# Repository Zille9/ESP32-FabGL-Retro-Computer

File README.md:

# ESP32-Basic with FabGL VGA library + PS2-Keyboard
### Basic32+ with FabGL VGA library + PS2 PS2Controller for VGA monitor output - 2019 - 2023       
#### Ursprungsversion von: Rob Cai <rocaj74@gmail.com>
#### erweitert/modifiziert von:Reinhard Zielinski <zille09@gmail.com>                                                                   
#### Das Ergebnis ist ein kleiner Retro-Computer mit folgender Ausstattung:
- (Schaltplan siehe Ordner Schematic) 

## Hardware:
```
-ESP32 / 240MHz
-56472 Basic Bytes free
-VGA-Display 320x240 Pixel 64 Farben , AV (IO26) oder TFT-Screen 320x240 Pixel
-IO-Erweiterung mit MCP23017 (2x8 IO-Ports) + EEPROM 512kB 
-CardKb als PS2-Tastatur nutzbar (siehe Ordner <src/CardKeyBoard_neu>)
-Unterstützung von externem SPI-RAM 128kB, 512kB (Adafruit SPI-Fram) oder 2, 4 oder 8 MB PSRAM im SPI-Mode
-PS2-Keyboard 
-RTC DS3231 
-SD-Card
```

## Software:
```
Die Ursprungsversion wurde durch folgende Funktionen erweitert  

-fliesskomma Arithmetik
-Grafikfunktionen 	
-mathematische Funktionen 	
-Stringfunktionen 	
-lange Variablennamen  	
-viele zusätzliche Befehle (DATA,READ,STRG$,LEFT$,RIGHT$,MID$,POS,TAB,SPC,SIN,COS,TAN,ATN,LOG,SQR,PI usw.) 	
-erweiterte logische Operatoren (AND, OR) 	
-BIT-Manipulation &,|,%,<<,>> usw. 	
-Klammerrechnung 	
-IF THEN ELSE Abfragen 	
-Speichermonitor 	
-Exponential-Ein/Ausgabe 	
-Verschiedene Sensoren und Komponenten HC-S04, Dallas DS18S20, DHT, LCD, Neopixel-LED, BMP180 	
-Zeileneditor 
-BMP-Bilddatei-Import / Export
-Spritefunktionen (noch in der Entwicklung)
-Soundfunktionen (noch in der Entwicklung)
-integrierte Kurzhilfe
-Syntax-Hervorhebung
-Binärprogramme können mit RUN"/xxx.bin" gestartet werden - siehe Ordner <Software>

```

***Special Thanks on Guido Lehwalder and Marcelo Dantas ->RUN-CPM is a great Work!***

***Also thanks on Fabrizio Di Vittorio for the excellent FabGl-Library***

## How to compile
```
-use Arduino IDE 1.8.19
-Espressiv ESP32 Version 1.0.6
-FabGL Version 1.0.9
-copy all Files in the libraries to Arduino lib Directory
-compile and enjoy
```

```
-Startbildschirm
```

```
-Basic-Befehle
```

```
-Basic -Funktionen
```

```
-Programm Globus.Bas
```

```
-Darstellung einer BMP-Datei
```

```
-Programmlisting
```

```
Screenshot als BMP-Datei exportiert
```

```
...mit RUN kann dann auch CPM gestartet werden.
```

```
...RUN-CPM Startbildschirm , mit EXIT kehrt man wieder zum Basic32+ zurück.
```

```
...der GRID-Befehl in Aktion .
```

## Bibliotheken einbinden und Basic32+ compilieren:
```
-die im Ordner libraries liegenden Unterverzeichnisse ins Arduino libraries-Verzeichnis kopieren

-zusätzlich die FabGL-lib mit dem Bibliotheksmanager der Arduino-IDE installieren

-die Quellen befinden sich im Ordner "src/FabGL-Basic" ->kompilieren und in den ESP32 laden

-den Inhalt des Verzeichnisses SD-Card auf eine SD-Karte kopieren .... und mit ESP32+Basic loslegen :-)

Im Ordner RUN-CPM befindet sich die um den OTA-Loader erweiterte Variante, um nach Eingabe von EXIT wieder zum Basic zurückzukehren.
```

## Komponenten:

-ESP32 NodeMCU https://www.berrybase.de/esp32-nodemcu-development-board?sPartner=g_shopping&gclid=EAIaIQobChMI-fTJwNmx_wIVkupRCh1mTAgZEAQYBSABEgKjwvD_BwE

-MCP23017 https://www.reichelt.de/i-o-erweiterung-16bit-1-8-5v-seriell-i2c-dip-28-mcp-23017-e-sp-p140074.html?&trstct=pos_0&nbc=1

-FRAM 512kB https://www.adafruit.com/product/4719

-SD-Card Modul https://www.reichelt.de/arduino-sd-karten-modul-ard-module-sd-p282683.html?PROVID=2788&gclid=EAIaIQobChMIqL3-sdqx_wIVQ9rVCh1oSQiAEAQYAiABEgL9BPD_BwE

-RTC-Modul https://www.reichelt.de/entwicklerboards-praezisions-echtzeituhr-ds3231-debo-rtc-uhr2-p235506.html?PROVID=2788&gclid=EAIaIQobChMImaDrzNqx_wIVQs7VCh1VowhwEAQYBCABEgLQoPD_BwE

-siehe auch BOOM-List im Ordner Schematic ->folgt bald

 ### Author:Reinhard Zielinski <zille09@gmail.com> April 2021

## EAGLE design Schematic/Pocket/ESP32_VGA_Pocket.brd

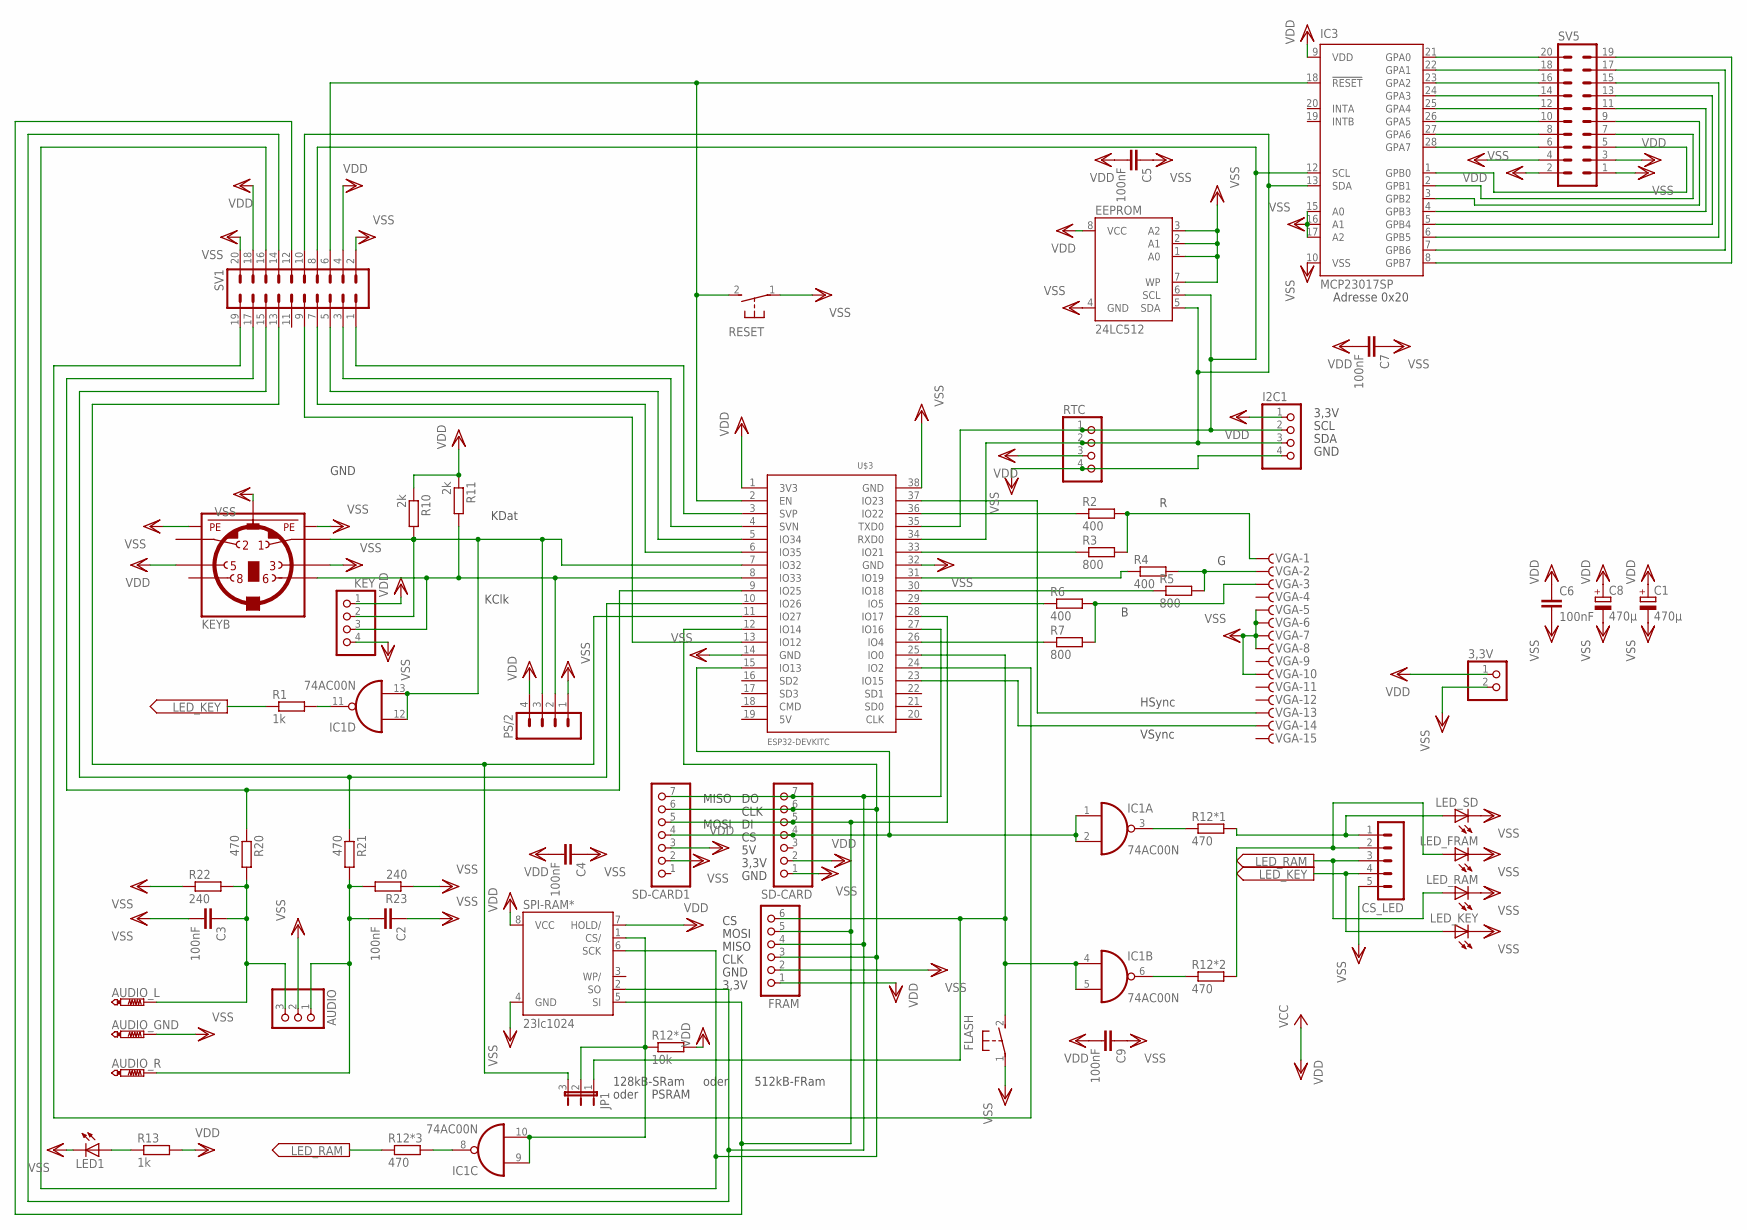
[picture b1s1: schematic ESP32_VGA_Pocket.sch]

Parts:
3,3V: PINHD-1X2; 1X02
AUDIO: PINHD-1X3; 1X03
AUDIO_GND: PTR1PAD1-13Y; P1-13Y
AUDIO_L: PTR1PAD1-13Y; P1-13Y
AUDIO_R: PTR1PAD1-13Y; P1-13Y
C1, C8: 470µ; E3,5-10
C2, C3, C4, C5, C6, C7, C9: 100nF; C025-030X050
CS_LED: MA05-1
EEPROM: 24LC512; DIL08
FLASH: 31-XX; B3F-31XX; MPN B3F-3100
FRAM: PINHD-1X6; 1X06
I2C1: PINHD-1X4; 1X04
IC1: 74AC00N; DIL14
IC3: MCP23017SP; DIL28-3; MPN MCP23017-E/SO
JP1: JP2E; JP2
KEY: PINHD-1X4; 1X04
KEYB: MINI_DIN_6; M_DIN6
LED1: LED5MM
LED_FRAM: LED5MM
LED_KEY: LED5MM
LED_RAM: LED5MM
LED_SD: LED5MM
PS/2: MA04-1
R1, R13: 1k; 0204/7
R2, R4, R6: 400; 0204/7
R3, R5, R7: 800; 0204/7
R10, R11: 2k; 0204/7
R12*: 10k; 0204/7
R12*1, R12*2, R12*3, R20, R21: 470; 0204/7
R22, R23: 240; 0204/7
RESET: 31-XX; B3F-31XX
RTC: PINHD-1X4; 1X04
SD-CARD, SD-CARD1: PINHD-1X7; 1X07
SPI-RAM*: 23lc1024; DIL08
SV1, SV5: MA10-2
U$3: ESP32DEVKITC; ESP32-DEVKITC
VGA: F15HDHS; HDF15H

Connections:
AUDIO1: AUDIO.3, AUDIO_L.TP, C3.1, R20.2, R22.2
AUDIO2: AUDIO.1, AUDIO_R.TP, C2.2, R21.2, R23.2
CLK: FRAM.3, SD-CARD.6, SD-CARD1.6, SPI-RAM*.6 (SCK), SV1.16, U$3.12 (IO14)
CLK_K: KEY.3, KEYB.6, PS/2.2, R11.2, U$3.8 (IO33)
CS_RAM: IC1.9 (I0), IC1.10 (I1), JP1.2, R12*.1, SPI-RAM*.1 (CS/)
CS_SD: IC1.1 (I0), IC1.2 (I1), SD-CARD.4, SD-CARD1.4, U$3.15 (IO13)
DAT_K: IC1.12 (I0), IC1.13 (I1), KEY.2, KEYB.1, PS/2.3, R10.2, U$3.7 (IO32)
FLASH: FLASH.2 (S), FRAM.6, IC1.4 (I0), IC1.5 (I1), JP1.1, U$3.25 (IO0)
GND: IC1.7 (GND)
IO2: SV1.19, U$3.24 (IO2)
IO12: SV1.9, U$3.13 (IO12)
IO27: JP1.3, SV1.13, U$3.11 (IO27)
IO34: SV1.5, U$3.5 (IO34)
IO35: SV1.7, U$3.6 (IO35)
IO36: SV1.1, U$3.3 (SVP)
IO39: SV1.3, U$3.4 (SVN)
LED_FRAM: CS_LED.2, LED_FRAM.A, R12*2.2
LED_KEY: CS_LED.4, LED_KEY.A, R1.1
LED_RAM: CS_LED.3, LED_RAM.A, R12*3.1
LED_SD: CS_LED.1, LED_SD.A, R12*1.2
MISO: FRAM.4, SD-CARD.7, SD-CARD1.7, SPI-RAM*.2 (SO), SV1.14, U$3.27 (IO16)
MOSI: FRAM.5, SD-CARD.5, SD-CARD1.5, SPI-RAM*.5 (SI), SV1.12, U$3.28 (IO17)
unnamed: R20.1, SV1.17, U$3.9 (IO25)
unnamed: IC1.3 (O), R12*1.1
unnamed: R21.1, SV1.15, U$3.10 (IO26)
unnamed: IC1.11 (O), R1.2
unnamed: IC1.6 (O), R12*2.1
unnamed: IC1.8 (O), R12*3.2
unnamed: LED1.A, R13.1
unnamed: IC3.1 (GPB0), SV5.5
unnamed: IC3.21 (GPA0), SV5.20
unnamed: IC3.22 (GPA1), SV5.18
unnamed: IC3.23 (GPA2), SV5.16
unnamed: IC3.24 (GPA3), SV5.14
unnamed: IC3.25 (GPA4), SV5.12
unnamed: IC3.26 (GPA5), SV5.10
unnamed: IC3.27 (GPA6), SV5.8
unnamed: IC3.28 (GPA7), SV5.6
unnamed: IC3.2 (GPB1), SV5.7
unnamed: IC3.3 (GPB2), SV5.9
unnamed: IC3.4 (GPB3), SV5.11
unnamed: IC3.5 (GPB4), SV5.13
unnamed: IC3.6 (GPB5), SV5.15
unnamed: IC3.7 (GPB6), SV5.17
unnamed: IC3.8 (GPB7), SV5.19
unnamed: R6.2, R7.2, VGA.3
unnamed: R4.2, R5.2, VGA.2
unnamed: R2.2, R3.2, VGA.1
unnamed: R2.1, U$3.36 (IO22)
unnamed: R3.1, U$3.33 (IO21)
unnamed: R4.1, U$3.31 (IO19)
unnamed: R5.1, U$3.30 (IO18)
unnamed: R6.1, U$3.29 (IO5)
unnamed: R7.1, U$3.26 (IO4)
unnamed: U$3.37 (IO23), VGA.13
unnamed: U$3.23 (IO15), VGA.14
RESET: IC3.18 (!RESET), RESET.2 (S), SV1.6, U$3.2 (EN)
SCL: EEPROM.6 (SCL), I2C1.2, IC3.12 (SCL), RTC.1, SV1.8, U$3.35 (TXD0)
SDA: EEPROM.5 (SDA), I2C1.3, IC3.13 (SDA), RTC.2, SV1.10, U$3.34 (RXD0)
VDD: 3,3V.1, C1.+, C4.2, C5.2, C6.1, C7.2, C8.+, C9.2, EEPROM.8 (VCC), FRAM.1, I2C1.1, IC1.14 (VCC), IC3.9 (VDD), KEY.1, KEYB.5, PS/2.4, R10.1, R11.1, R12*.2, R13.2, RTC.3, SD-CARD.2, SD-CARD1.3, SPI-RAM*.7 (HOLD/), SPI-RAM*.8 (VCC), SV1.4, SV1.18, SV5.3, SV5.4, U$3.1 (3V3)
VSS: 3,3V.2, AUDIO.2, AUDIO_GND.TP, C1.-, C2.1, C3.2, C4.1, C5.1, C6.2, C7.1, C8.-, C9.1, CS_LED.5, EEPROM.1 (A0), EEPROM.2 (A1), EEPROM.3 (A2), EEPROM.4 (GND), EEPROM.7 (WP), FLASH.1, FRAM.2, I2C1.4, IC3.10 (VSS), IC3.15 (A0), IC3.16 (A1), IC3.17 (A2), KEY.4, KEYB.3, KEYB.SH1 (PE1), KEYB.SH2 (PE2), KEYB.SH3 (PE3), LED1.K (C), LED_FRAM.K (C), LED_KEY.K (C), LED_RAM.K (C), LED_SD.K (C), PS/2.1, R22.1, R23.1, RESET.1, RTC.4, SD-CARD.1, SD-CARD1.2, SPI-RAM*.4 (GND), SV1.2, SV1.20, SV5.1, SV5.2, U$3.14 (GND), U$3.32 (GND), U$3.38 (GND), VGA.5, VGA.6, VGA.7, VGA.8, VGA.10

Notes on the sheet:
CLK
MISO
MOSI
KDat
KClk
VSync
HSync
GND
SCL
SDA
3,3V
128kB-SRam
512kB-FRam
oder
Adresse 0x20
PSRAM

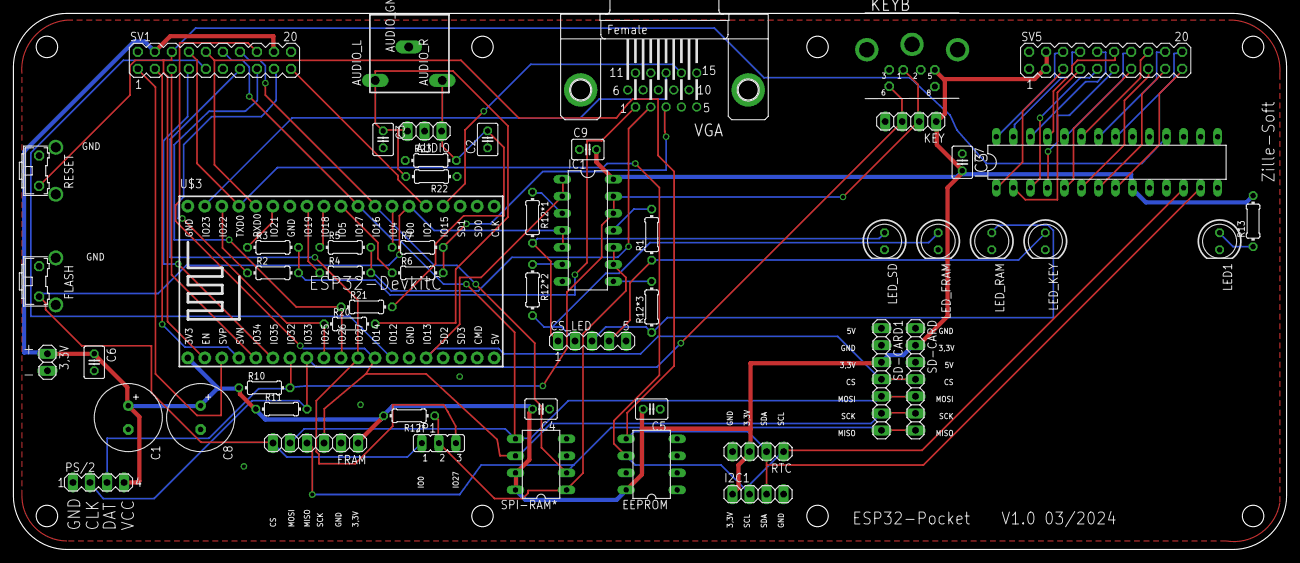
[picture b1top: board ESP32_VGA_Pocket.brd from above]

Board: 2 copper layers, 190.0 x 80.0 mm, 57 parts (0 on the bottom side), 60 nets.

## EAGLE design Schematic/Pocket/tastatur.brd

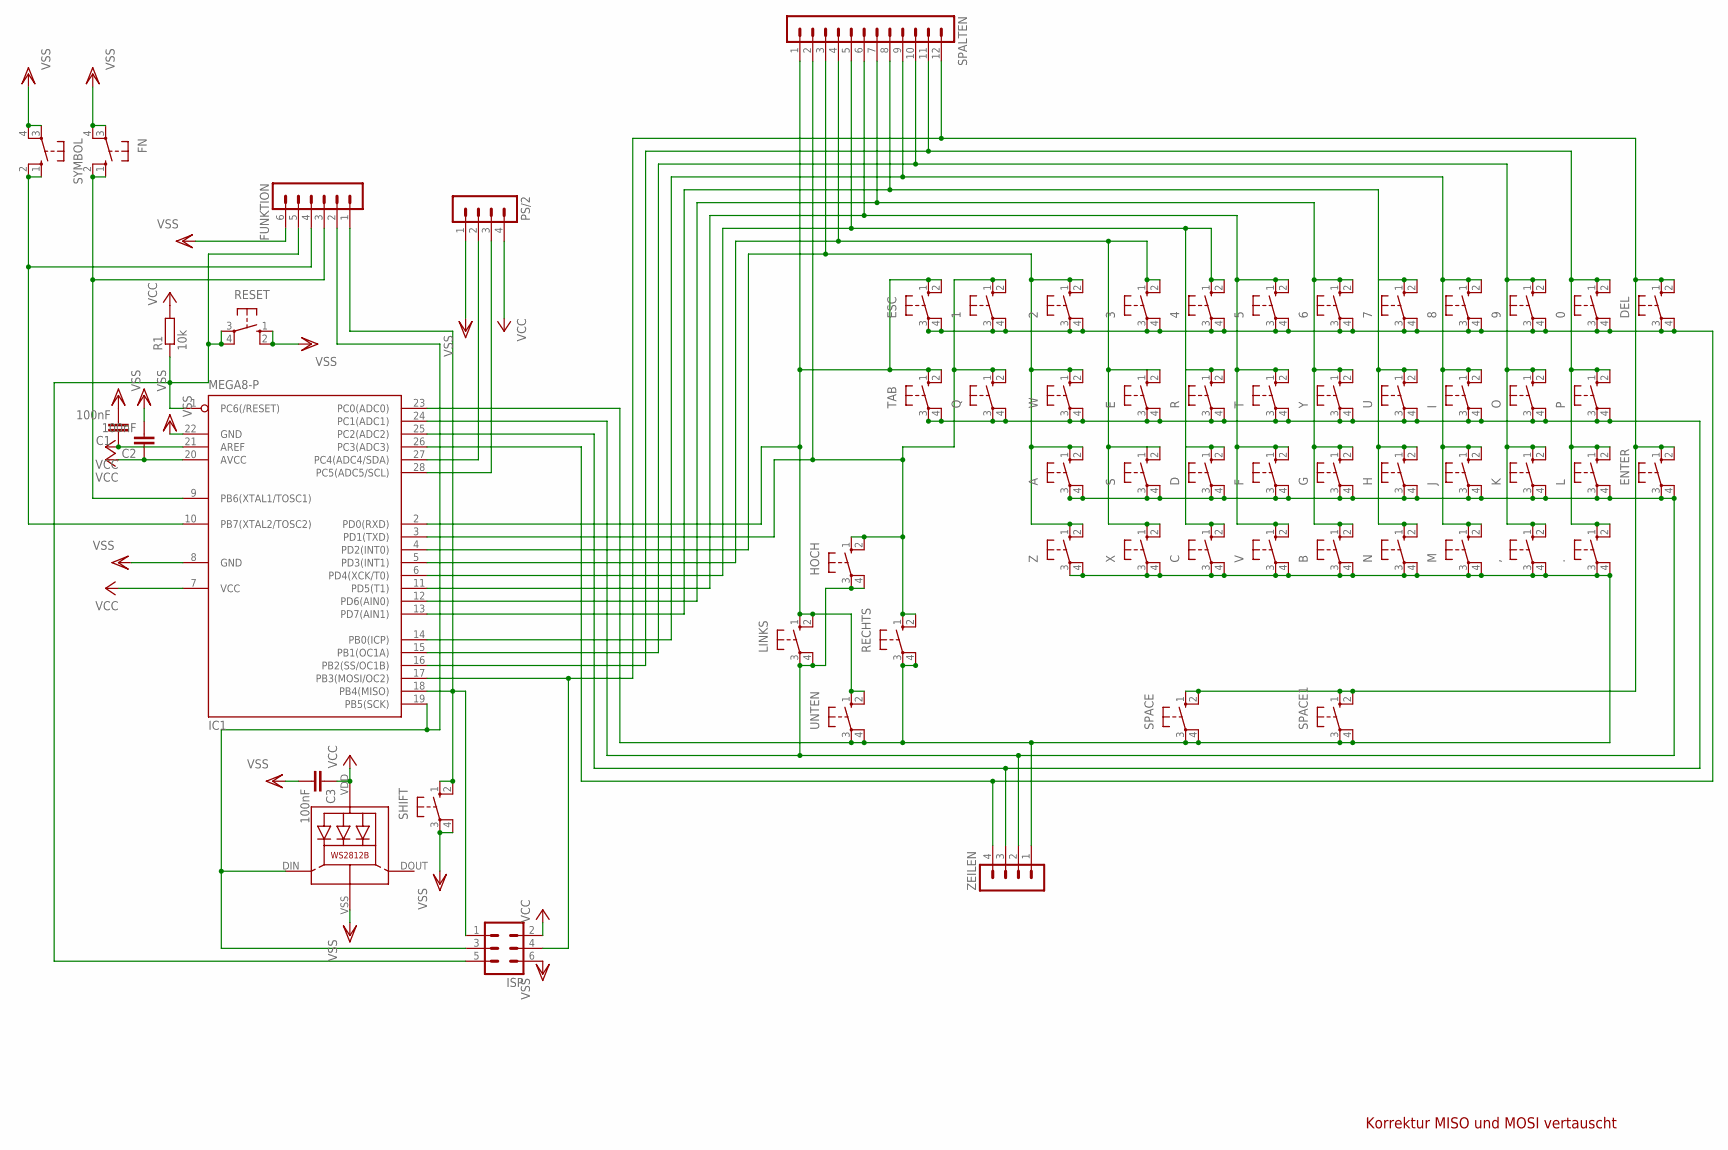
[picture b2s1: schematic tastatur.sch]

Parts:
0, 1, 2, 3, 4, 5, 6, 7, 8, 9, .: 40-XX; B3F-40XX
,: 40-XX; B3F-40XX
A: 40-XX; B3F-40XX
B: 40-XX; B3F-40XX
C: 40-XX; B3F-40XX
C1, C2, C3: 100nF; C025-025X050
D: 40-XX; B3F-40XX
DEL: 40-XX; B3F-40XX
E: 40-XX; B3F-40XX
ENTER: 40-XX; B3F-40XX
ESC: 40-XX; B3F-40XX
F: 40-XX; B3F-40XX
FN: 40-XX; B3F-40XX
FUNKTION: MA06-1
G: 40-XX; B3F-40XX
H: 40-XX; B3F-40XX
HOCH: 40-XX; B3F-40XX; MPN B3F-4000
I: 40-XX; B3F-40XX
IC1: MEGA8-P; DIL28-3
ISP: ML6L
J: 40-XX; B3F-40XX
K: 40-XX; B3F-40XX
L: 40-XX; B3F-40XX
LED1: WS2812B
LINKS: 40-XX; B3F-40XX; MPN B3F-4000
M: 40-XX; B3F-40XX
N: 40-XX; B3F-40XX
O: 40-XX; B3F-40XX
P: 40-XX; B3F-40XX
PS/2: MA04-1
Q: 40-XX; B3F-40XX
R: 40-XX; B3F-40XX
R1: 10k; 0204/7
RECHTS: 40-XX; B3F-40XX; MPN B3F-4000
RESET: 10-XX; B3F-10XX
S: 40-XX; B3F-40XX
SHIFT: 40-XX; B3F-40XX
SPACE: 40-XX; B3F-40XX; MPN B3F-4000
SPACE1: 40-XX; B3F-40XX
SPALTEN: MA12-1
SYMBOL: 40-XX; B3F-40XX
T: 40-XX; B3F-40XX
TAB: 40-XX; B3F-40XX
U: 40-XX; B3F-40XX
UNTEN: 40-XX; B3F-40XX; MPN B3F-4000
V: 40-XX; B3F-40XX
W: 40-XX; B3F-40XX
X: 40-XX; B3F-40XX
Y: 40-XX; B3F-40XX
Z: 40-XX; B3F-40XX
ZEILEN: MA04-1

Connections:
A0: ,.3, ,.4 (P1), ..3, ..4 (P1), B.3, B.4 (P1), C.3, C.4 (P1), IC1.23 (PC0(ADC0)), M.3, M.4 (P1), N.3, N.4 (P1), RECHTS.3, RECHTS.4 (P1), SPACE.3, SPACE.4 (P1), SPACE1.3, SPACE1.4 (P1), UNTEN.3, UNTEN.4 (P1), V.3, V.4 (P1), X.3, X.4 (P1), Z.3, Z.4 (P1), ZEILEN.1
A1: A.3, A.4 (P1), D.3, D.4 (P1), ENTER.3, ENTER.4 (P1), F.3, F.4 (P1), G.3, G.4 (P1), H.3, H.4 (P1), HOCH.3, HOCH.4 (P1), IC1.24 (PC1(ADC1)), J.3, J.4 (P1), K.3, K.4 (P1), L.3, L.4 (P1), LINKS.3, LINKS.4 (P1), S.3, S.4 (P1), ZEILEN.2
A2: E.3, E.4 (P1), I.3, I.4 (P1), IC1.25 (PC2(ADC2)), O.3, O.4 (P1), P.3, P.4 (P1), Q.3, Q.4 (P1), R.3, R.4 (P1), T.3, T.4 (P1), TAB.3, TAB.4 (P1), U.3, U.4 (P1), W.3, W.4 (P1), Y.3, Y.4 (P1), ZEILEN.3
A3: 0.3, 0.4 (P1), 1.3, 1.4 (P1), 2.3, 2.4 (P1), 3.3, 3.4 (P1), 4.3, 4.4 (P1), 5.3, 5.4 (P1), 6.3, 6.4 (P1), 7.3, 7.4 (P1), 8.3, 8.4 (P1), 9.3, 9.4 (P1), DEL.3, DEL.4 (P1), ESC.3, ESC.4 (P1), IC1.26 (PC3(ADC3)), ZEILEN.4
CLK: IC1.27 (PC4(ADC4/SDA)), PS/2.2
D0: ESC.1 (S), ESC.2 (S1), IC1.2 (PD0(RXD)), LINKS.1 (S), LINKS.2 (S1), SPALTEN.1, TAB.1 (S), TAB.2 (S1), UNTEN.1 (S), UNTEN.2 (S1)
D1: 1.1 (S), 1.2 (S1), HOCH.1 (S), HOCH.2 (S1), IC1.3 (PD1(TXD)), Q.1 (S), Q.2 (S1), RECHTS.1 (S), RECHTS.2 (S1), SPALTEN.2
D2: 2.1 (S), 2.2 (S1), A.1 (S), A.2 (S1), IC1.4 (PD2(INT0)), SPALTEN.3, W.1 (S), W.2 (S1), Z.1 (S), Z.2 (S1)
D3: 3.1 (S), 3.2 (S1), E.1 (S), E.2 (S1), IC1.5 (PD3(INT1)), S.1 (S), S.2 (S1), SPALTEN.4, X.1 (S), X.2 (S1)
D4: 4.1 (S), 4.2 (S1), C.1 (S), C.2 (S1), D.1 (S), D.2 (S1), IC1.6 (PD4(XCK/T0)), R.1 (S), R.2 (S1), SPALTEN.5
D5: 5.1 (S), 5.2 (S1), F.1 (S), F.2 (S1), IC1.11 (PD5(T1)), SPALTEN.6, T.1 (S), T.2 (S1), V.1 (S), V.2 (S1)
D6: 6.1 (S), 6.2 (S1), B.1 (S), B.2 (S1), G.1 (S), G.2 (S1), IC1.12 (PD6(AIN0)), SPALTEN.7, Y.1 (S), Y.2 (S1)
D7: 7.1 (S), 7.2 (S1), H.1 (S), H.2 (S1), IC1.13 (PD7(AIN1)), N.1 (S), N.2 (S1), SPALTEN.8, U.1 (S), U.2 (S1)
D8: 8.1 (S), 8.2 (S1), I.1 (S), I.2 (S1), IC1.14 (PB0(ICP)), J.1 (S), J.2 (S1), M.1 (S), M.2 (S1), SPALTEN.9
D9: 9.1 (S), 9.2 (S1), ,.1 (S), ,.2 (S1), IC1.15 (PB1(OC1A)), K.1 (S), K.2 (S1), O.1 (S), O.2 (S1), SPALTEN.10
D10: 0.1 (S), 0.2 (S1), ..1 (S), ..2 (S1), IC1.16 (PB2(SS/OC1B)), L.1 (S), L.2 (S1), P.1 (S), P.2 (S1), SPALTEN.11
D11: DEL.1 (S), DEL.2 (S1), ENTER.1 (S), ENTER.2 (S1), IC1.17 (PB3(MOSI/OC2)), ISP.4, SPACE.1 (S), SPACE.2 (S1), SPACE1.1 (S), SPACE1.2 (S1), SPALTEN.12
DAT: IC1.28 (PC5(ADC5/SCL)), PS/2.3
DIN: FUNKTION.2, IC1.19 (PB5(SCK)), ISP.3, LED1.DIN (DI)
FN: FN.1 (S), FN.2 (S1), FUNKTION.3, IC1.9 (PB6(XTAL1/TOSC1))
RESET: FUNKTION.5, IC1.1 (PC6(/RESET)), ISP.5, R1.1, RESET.3, RESET.4 (P1)
SHIFT: FUNKTION.1, IC1.18 (PB4(MISO)), ISP.1, SHIFT.1 (S), SHIFT.2 (S1)
SYMBOL: FUNKTION.4, IC1.10 (PB7(XTAL2/TOSC2)), SYMBOL.1 (S), SYMBOL.2 (S1)
VCC: C1.1, C2.1, C3.1, IC1.7 (VCC), IC1.20 (AVCC), IC1.21 (AREF), ISP.2, LED1.VDD, PS/2.4, R1.2
VSS: C1.2, C2.2, C3.2, FN.3, FN.4 (P1), FUNKTION.6, IC1.8 (GND), IC1.22 (GND), ISP.6, LED1.VSS (GND), PS/2.1, RESET.1 (S), RESET.2 (S1), SHIFT.3, SHIFT.4 (P1), SYMBOL.3, SYMBOL.4 (P1)

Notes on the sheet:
Korrektur MISO und MOSI vertauscht

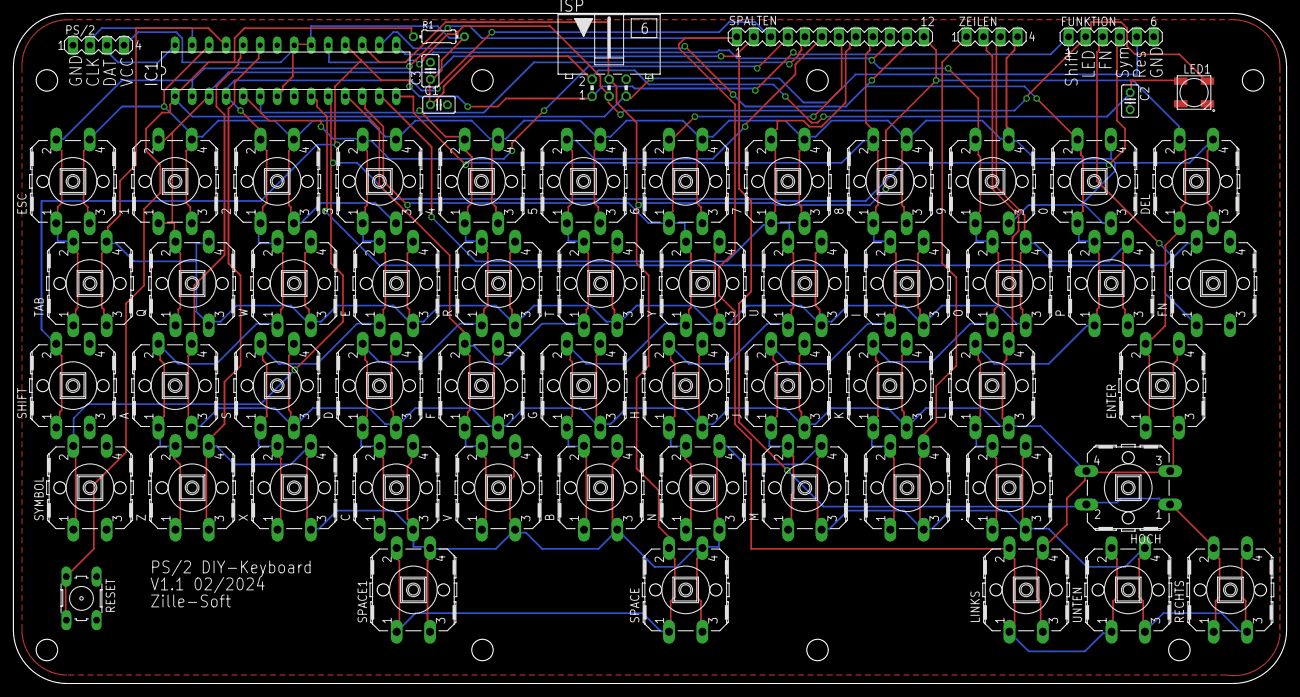
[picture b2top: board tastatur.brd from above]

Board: 2 copper layers, 190.0 x 100.0 mm, 63 parts (0 on the bottom side), 25 nets.

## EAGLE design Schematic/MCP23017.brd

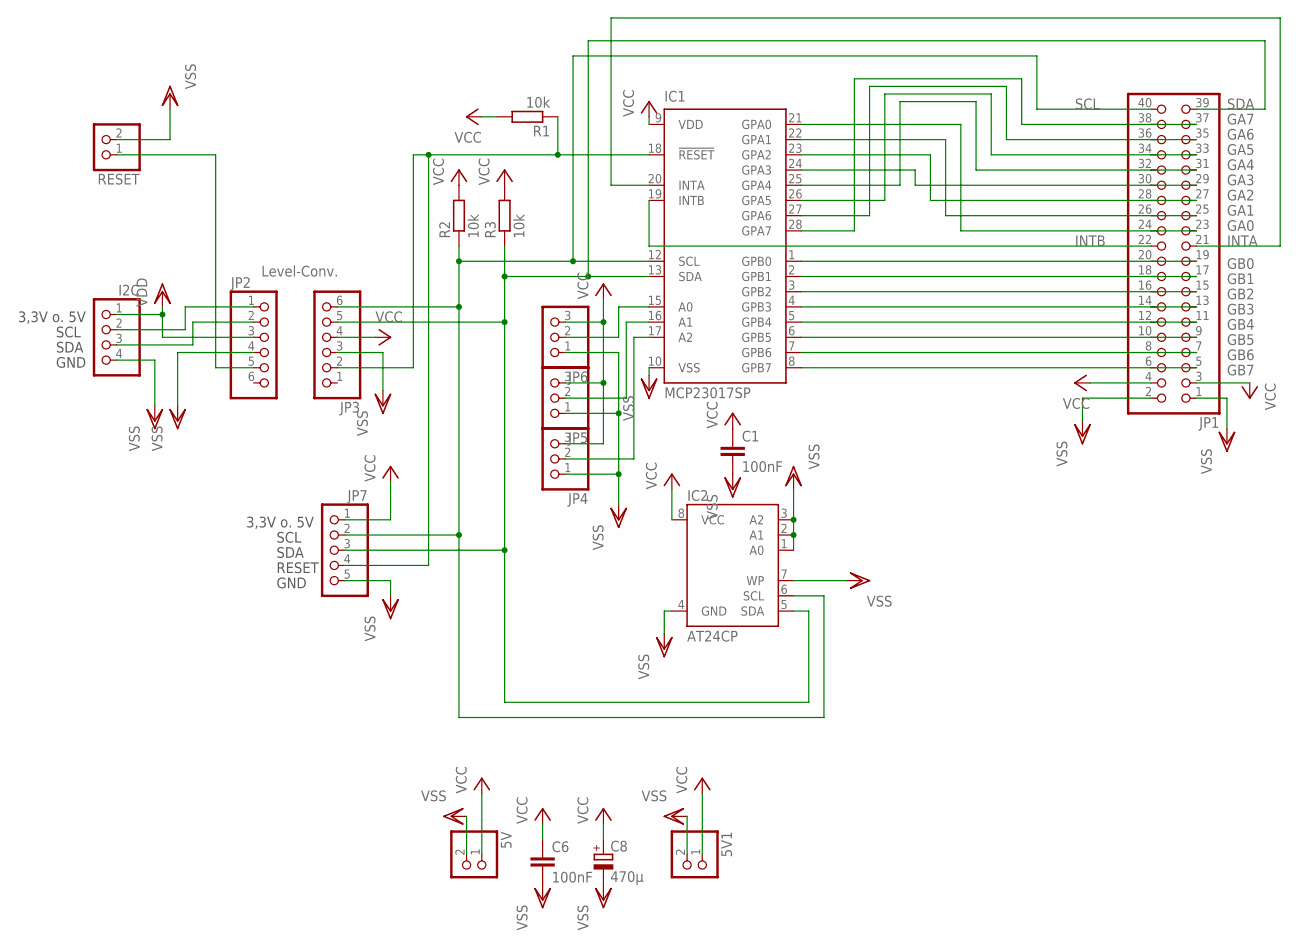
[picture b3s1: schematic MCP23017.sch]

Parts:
5V, 5V1: PINHD-1X2; 1X02
C1, C6: 100nF; C025-030X050
C8: 470µ; E3,5-10
I2C: PINHD-1X4; 1X04
IC1: MCP23017SP; DIL28-3
IC2: AT24CP; DIL08
JP1: PINHD-2X20; 2X20
JP2, JP3: PINHD-1X6; 1X06
JP4, JP5, JP6: PINHD-1X3; 1X03
JP7: PINHD-1X5; 1X05
R1, R2, R3: 10k; 0207/10
RESET: PINHD-1X2; 1X02

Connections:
A0: IC1.21 (GPA0), JP1.23, JP1.24
A1: IC1.22 (GPA1), JP1.25, JP1.26
A2: IC1.23 (GPA2), JP1.27, JP1.28
A3: IC1.24 (GPA3), JP1.29, JP1.30
A4: IC1.25 (GPA4), JP1.31, JP1.32
A5: IC1.26 (GPA5), JP1.33, JP1.34
A6: IC1.27 (GPA6), JP1.35, JP1.36
A7: IC1.28 (GPA7), JP1.37, JP1.38
B0: IC1.1 (GPB0), JP1.19, JP1.20
B1: IC1.2 (GPB1), JP1.17, JP1.18
B2: IC1.3 (GPB2), JP1.15, JP1.16
B3: IC1.4 (GPB3), JP1.13, JP1.14
B4: IC1.5 (GPB4), JP1.11, JP1.12
B5: IC1.6 (GPB5), JP1.9, JP1.10
B6: IC1.7 (GPB6), JP1.7, JP1.8
B7: IC1.8 (GPB7), JP1.5, JP1.6
INTA: IC1.20 (INTA), JP1.21
INTB: IC1.19 (INTB), JP1.22
unnamed: IC1.15 (A0), JP6.2
unnamed: IC1.16 (A1), JP5.2
unnamed: IC1.17 (A2), JP4.2
RESET: IC1.18 (!RESET), JP3.2, JP7.4, R1.1
RESET-IN: JP2.5, RESET.1
SCL: IC1.12 (SCL), IC2.6 (SCL), JP1.40, JP3.6, JP7.2, R2.1
SCL-IN: I2C.2, JP2.1
SDA: IC1.13 (SDA), IC2.5 (SDA), JP1.39, JP3.5, JP7.3, R3.1
SDA-IN: I2C.3, JP2.2
VCC: 5V.1, 5V1.1, C1.1, C6.1, C8.+, IC1.9 (VDD), IC2.8 (VCC), JP1.3, JP1.4, JP3.4, JP4.3, JP5.3, JP6.3, JP7.1, R1.2, R2.2, R3.2
VDD: I2C.1, JP2.3
VSS: 5V.2, 5V1.2, C1.2, C6.2, C8.-, I2C.4, IC1.10 (VSS), IC2.1 (A0), IC2.2 (A1), IC2.3 (A2), IC2.4 (GND), IC2.7 (WP), JP1.1, JP1.2, JP2.4, JP3.3, JP4.1, JP5.1, JP6.1, JP7.5, RESET.2

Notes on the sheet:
SCL
SDA
3,3V o. 5V
GND
Level-Conv.
RESET
GB7
GB6
GB5
GB4
GB3
GB2
GB1
GB0
INTB
INTA
GA0
GA1
GA2
GA3
GA4
GA5
GA6
GA7

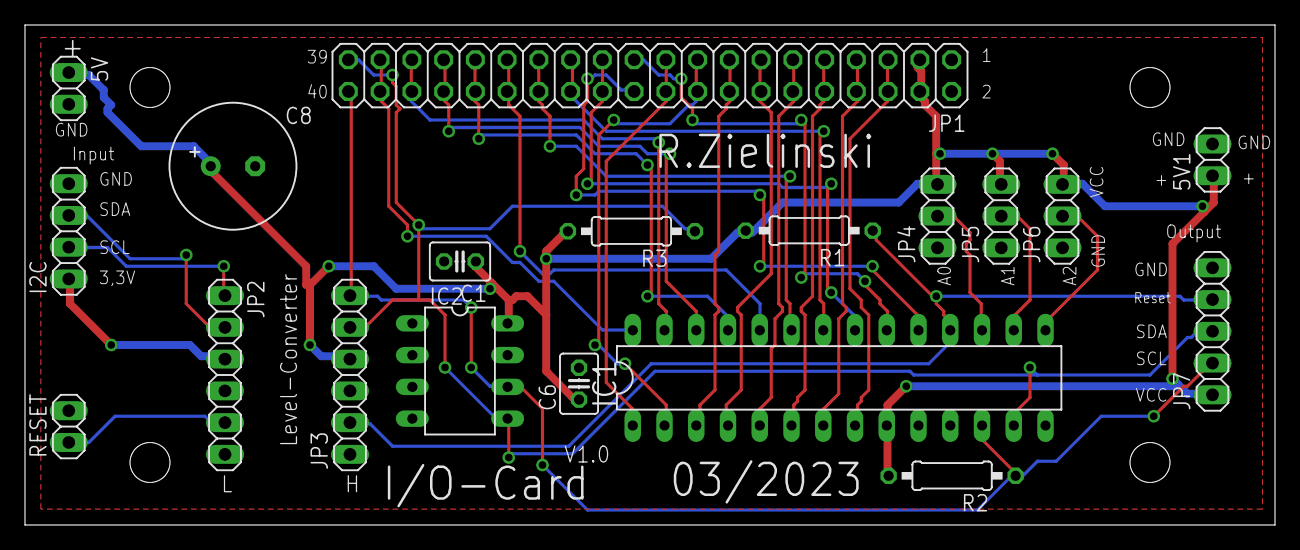
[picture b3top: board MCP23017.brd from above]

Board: 2 copper layers, 100.0 x 40.0 mm, 19 parts (0 on the bottom side), 30 nets.

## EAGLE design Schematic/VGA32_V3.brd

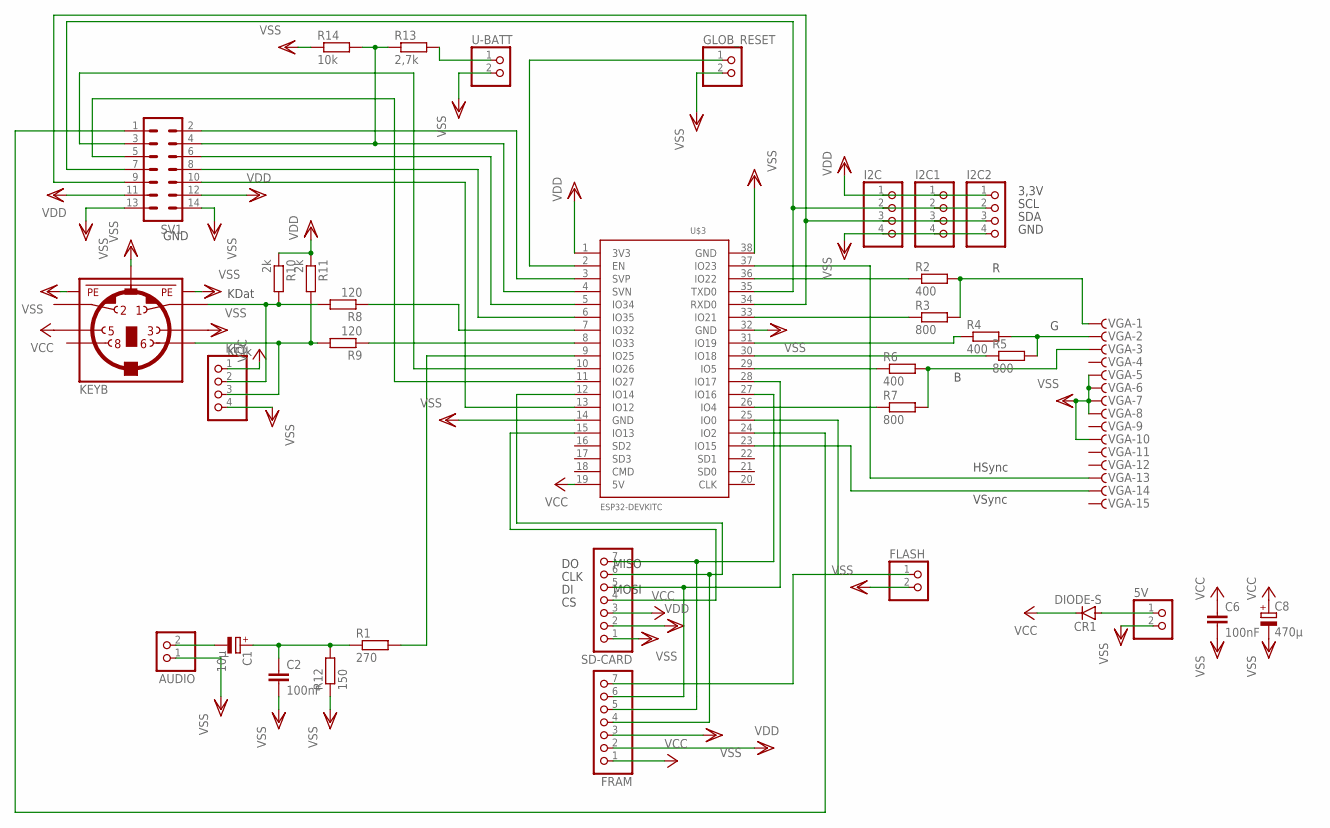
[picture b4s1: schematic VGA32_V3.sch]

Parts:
5V: PINHD-1X2; 1X02
AUDIO: PINHD-1X2; 1X02
C1: 10µ; E2-4
C2, C6: 100nF; C025-030X050
C8: 470µ; E3,5-10
CR1: DIODE-S; DO35-10
FLASH: PINHD-1X2; 1X02
FRAM: PINHD-1X7; 1X07
GLOB_RESET: PINHD-1X2; 1X02
I2C, I2C1, I2C2: PINHD-1X4; 1X04
KEY: PINHD-1X4; 1X04
KEYB: MINI_DIN_6; M_DIN6
R1: 270; 0204/7
R2, R4, R6: 400; 0204/7
R3, R5, R7: 800; 0204/7
R8, R9: 120; 0204/7
R10, R11: 2k; 0204/7
R12: 150; 0204/7
R13: 2,7k; 0204/7
R14: 10k; 0204/7
SD-CARD: PINHD-1X7; 1X07
SV1: ML14L
U$3: ESP32DEVKITC; ESP32-DEVKITC
U-BATT: PINHD-1X2; 1X02
VGA: F15HDHS; HDF15H

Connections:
5V: 5V.1, CR1.A
FLASH: FLASH.1, FRAM.7, U$3.25 (IO0)
IO2: SV1.1, U$3.24 (IO2)
IO12: SV1.10, U$3.13 (IO12)
IO26: SV1.3, U$3.10 (IO26)
IO27: SV1.5, U$3.11 (IO27)
IO34: SV1.6, U$3.5 (IO34)
IO35: SV1.8, U$3.6 (IO35)
IO36: SV1.2, U$3.3 (SVP)
IO39: R13.1, R14.2, SV1.4, U$3.4 (SVN)
unnamed: R1.2, U$3.9 (IO25)
unnamed: R13.2, U-BATT.1
unnamed: C1.+, C2.1, R1.1, R12.2
unnamed: AUDIO.2, C1.-
unnamed: R6.2, R7.2, VGA.3
unnamed: R4.2, R5.2, VGA.2
unnamed: R2.2, R3.2, VGA.1
unnamed: R2.1, U$3.36 (IO22)
unnamed: R3.1, U$3.33 (IO21)
unnamed: R4.1, U$3.31 (IO19)
unnamed: R5.1, U$3.30 (IO18)
unnamed: R6.1, U$3.29 (IO5)
unnamed: R7.1, U$3.26 (IO4)
unnamed: U$3.37 (IO23), VGA.13
unnamed: U$3.23 (IO15), VGA.14
unnamed: FRAM.5, SD-CARD.7, U$3.27 (IO16)
unnamed: FRAM.4, SD-CARD.6, U$3.12 (IO14)
unnamed: FRAM.6, SD-CARD.5, U$3.28 (IO17)
unnamed: SD-CARD.4, U$3.15 (IO13)
unnamed: KEY.2, KEYB.1, R8.2, R10.2
unnamed: R8.1, U$3.7 (IO32)
unnamed: KEY.3, KEYB.6, R9.2, R11.2
unnamed: R9.1, U$3.8 (IO33)
RESET: GLOB_RESET.1, U$3.2 (EN)
SCL: I2C.2, I2C1.2, I2C2.2, SV1.7, U$3.35 (TXD0)
SDA: I2C.3, I2C1.3, I2C2.3, SV1.9, U$3.34 (RXD0)
VCC: C6.1, C8.+, CR1.C, FRAM.1, KEY.1, KEYB.5, SD-CARD.3, U$3.19 (5V)
VDD: FRAM.2, I2C.1, I2C1.1, I2C2.1, R10.1, R11.1, SD-CARD.2, SV1.11, SV1.12, U$3.1 (3V3)
VSS: 5V.2, AUDIO.1, C2.2, C6.2, C8.-, FLASH.2, FRAM.3, GLOB_RESET.2, I2C.4, I2C1.4, I2C2.4, KEY.4, KEYB.3, KEYB.SH1 (PE1), KEYB.SH2 (PE2), KEYB.SH3 (PE3), R12.1, R14.1, SD-CARD.1, SV1.13, SV1.14, U$3.14 (GND), U$3.32 (GND), U$3.38 (GND), U-BATT.2, VGA.5, VGA.6, VGA.7, VGA.8, VGA.10

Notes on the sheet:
CLK
MISO
MOSI
KDat
KClk
VSync
HSync
GND
SCL
SDA
3,3V

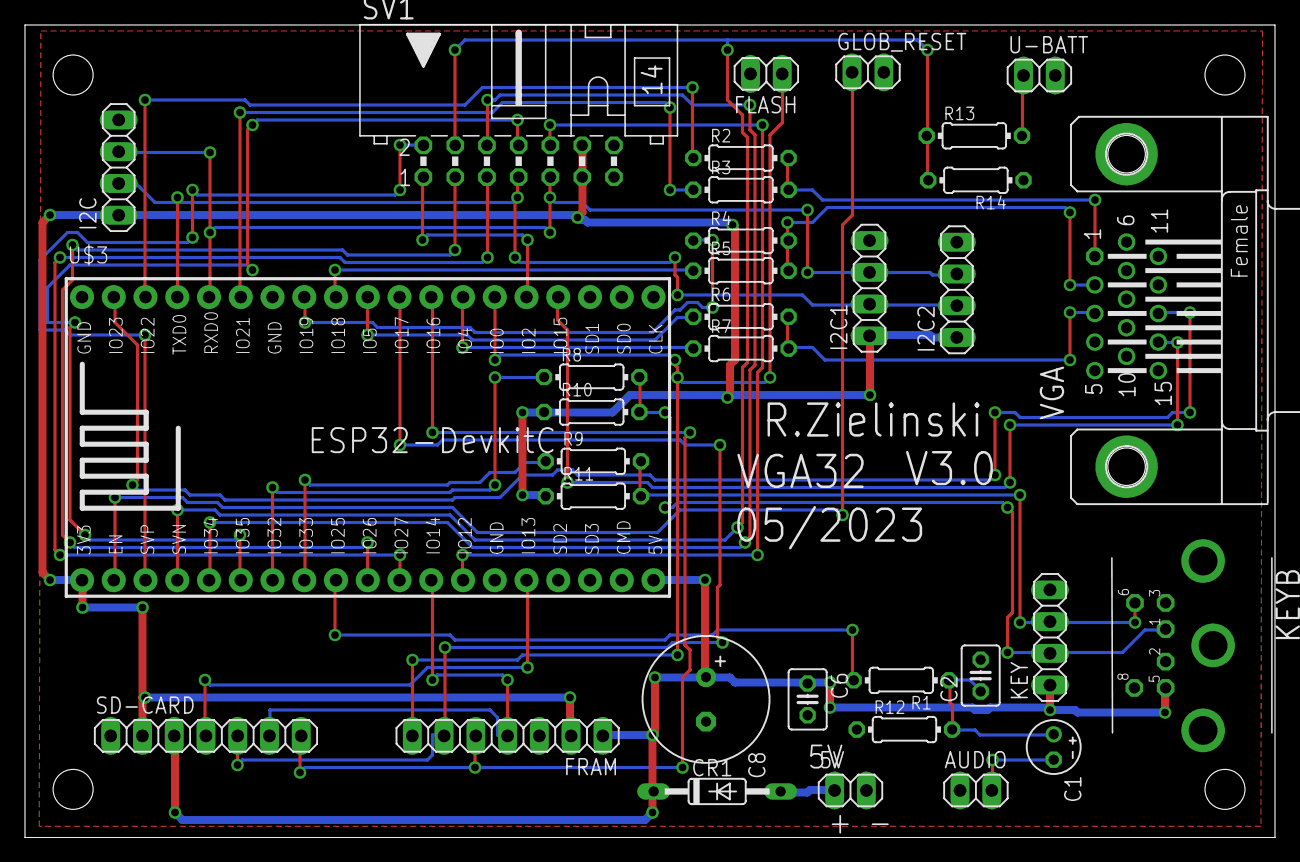
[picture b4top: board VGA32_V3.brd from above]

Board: 2 copper layers, 100.0 x 65.0 mm, 34 parts (0 on the bottom side), 39 nets.

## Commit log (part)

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2023-06-07 SD-Karte hinzugefügt
2023-06-07 SD-Karte
2023-06-07 Logbuch aktualisiert
2023-06-07 Schematic
2023-06-12 modify font_8x8.h
2023-06-27 Ordner organisieren
2023-06-27 Run-CPM add
2023-06-27 Banner
2023-07-01 update 1_75
2023-07-02 update1_75
2023-07-04 update1_77
2023-07-08 update1_80
2023-07-08 pictures
2023-07-09 update1_81
2023-07-09 update Logbuch
2023-07-13 update1_82
2023-07-14 minor update
2023-07-17 update1_83
2023-08-08 update1_87
2023-12-31 CardKB_include
2024-01-04 V1.91
2024-01-04 EEPROM_Adress_korrektur
2024-01-04 update help_sys
2024-01-16 add SpaceInvaders
2024-01-16 Ordner Software
2024-01-19 add Software
2024-01-21 Round Command
2024-01-23 Korrektur getln
2024-01-24 add ZXESPectrum
2024-01-31 modify DIR-Command
2024-02-20 bload+start entfernt
2024-02-23 add emulators and games
2024-02-25 add Kilo-Text-Editor
2024-02-26 add color-scheme F1-Key
2024-03-01 add Network Terminal
2024-03-03 add App-Starter, modify DIR
2024-03-03 add Pictures
2024-03-09 add mp3 player
2024-03-09 remove unused pdf
2024-03-09 remove oric pdf
2024-03-10 remove unused docs
2024-03-13 add mp3player/webradio wifi config
2024-03-27 Hardware_Update
2024-03-27 RAM-Upgrade
2026-01-30 Fehler in Printroutine behoben
2026-02-01 remove ? as Printing Command
2026-02-03 libraries actualized
2026-02-04 update libraries
2026-02-06 update mp3player
2026-02-06 update webradio / mp3player
2026-02-13 update Basic
2026-02-27 add Basic-Programs
2026-03-20 update
    Basic-Befehlssuche umgestellt, dadurch massiver Geschwindigkeitsschub
2026-03-21 syntax highlightning
2026-03-21 Add syntax highlighting to README
2026-03-21 Fix image filename case in README.md
2026-03-22 Fix image file extension from .jpg to .jpeg
2026-03-22 refresh files
2026-03-23 change SDA Port on IO27
2026-03-24 PAUSE-Befehl geändert
2026-03-24 update - PAUSE
2026-03-25 update array_dim
2026-03-26 Function AKKU deactivated
2026-03-27 modify RUN-Command
    RUN accept String Variables as Filename
2026-03-27 change PATH-Command
2026-03-29 add primzahl.bas
2026-04-22 listout changed
